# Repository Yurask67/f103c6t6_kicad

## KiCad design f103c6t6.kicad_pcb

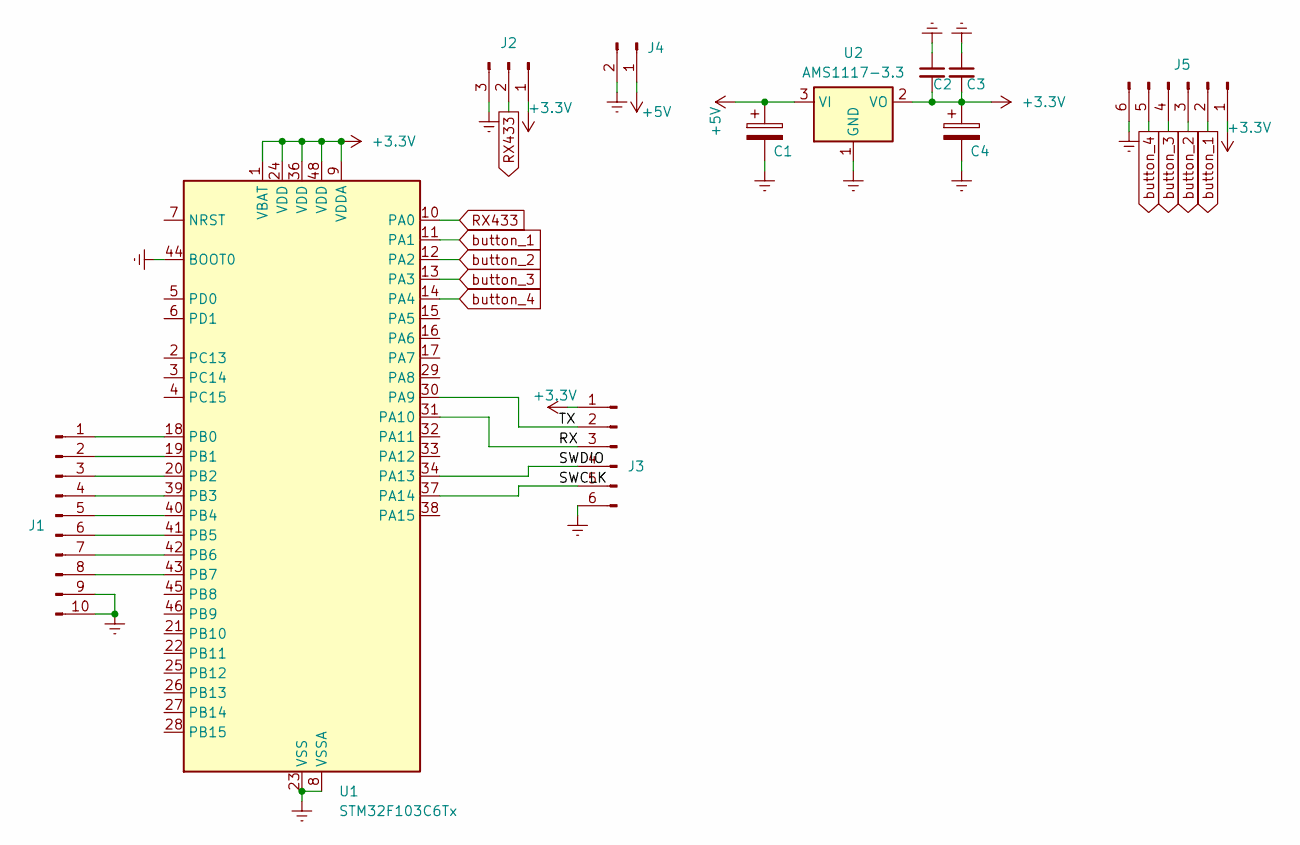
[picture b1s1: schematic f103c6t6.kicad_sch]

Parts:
C1, C4: C_Polarized; CP_Radial_D7.5mm_P2.50mm
C2, C3: C_Small; C_0805_2012Metric_Pad1.18x1.45mm_HandSolder
J1: Conn_01x10_Pin; PinHeader_2x05_P2.54mm_Vertical
J2: Conn_01x03_Pin; PinHeader_1x03_P2.54mm_Vertical
J3, J5: Conn_01x06_Pin; PinHeader_1x06_P2.54mm_Vertical
J4: Conn_01x02_Pin; PinHeader_1x02_P2.54mm_Vertical
U1: STM32F103C6Tx; LQFP-48_7x7mm_P0.5mm
U2: AMS1117-3.3; SOT-223-3_TabPin2

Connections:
+3.3V: C2.2, C3.2, C4.1, J2.1, J3.1, J5.1, U1.1 (VBAT), U1.9 (VDDA), U1.24 (VDD), U1.36 (VDD), U1.48 (VDD), U2.2 (VO)
+5V: C1.1, J4.1, U2.3 (VI)
/RX: J3.3, U1.31 (PA10)
/SWCLK: J3.5, U1.37 (PA14)
/SWDIO: J3.4, U1.34 (PA13)
/TX: J3.2, U1.30 (PA9)
GNDREF: C1.2, C2.1, C3.1, C4.2, J1.9, J1.10, J2.3, J3.6, J4.2, J5.6, U1.8 (VSSA), U1.23 (VSS), U1.35 (VSS), U1.44 (BOOT0), U1.47 (VSS), U2.1 (GND)
unnamed: J1.1, U1.18 (PB0)
unnamed: J1.2, U1.19 (PB1)
unnamed: J1.3, U1.20 (PB2)
unnamed: J1.4, U1.39 (PB3)
unnamed: J1.5, U1.40 (PB4)
unnamed: J1.6, U1.41 (PB5)
unnamed: J1.7, U1.42 (PB6)
unnamed: J1.8, U1.43 (PB7)
RX433: J2.2, U1.10 (PA0)
button_1: J5.2, U1.11 (PA1)
button_2: J5.3, U1.12 (PA2)
button_3: J5.4, U1.13 (PA3)
button_4: J5.5, U1.14 (PA4)

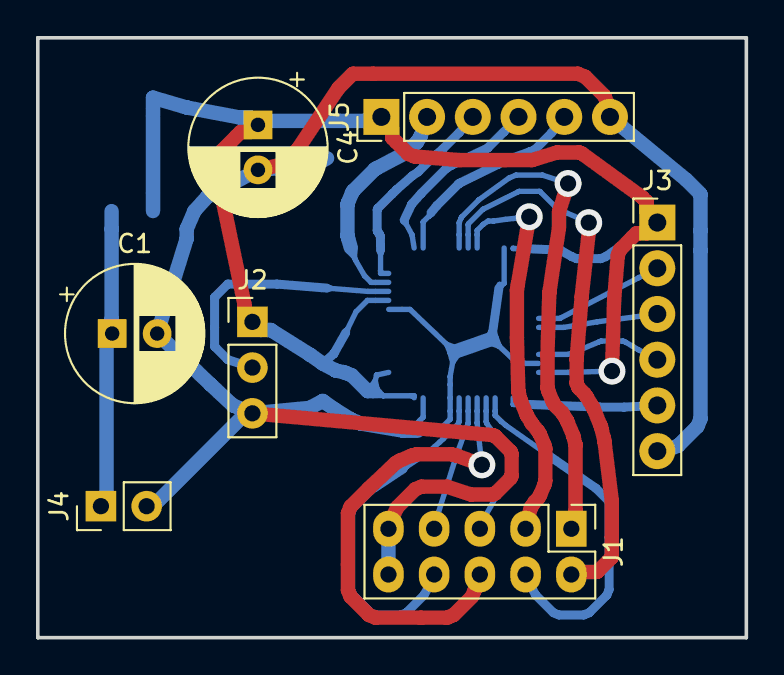
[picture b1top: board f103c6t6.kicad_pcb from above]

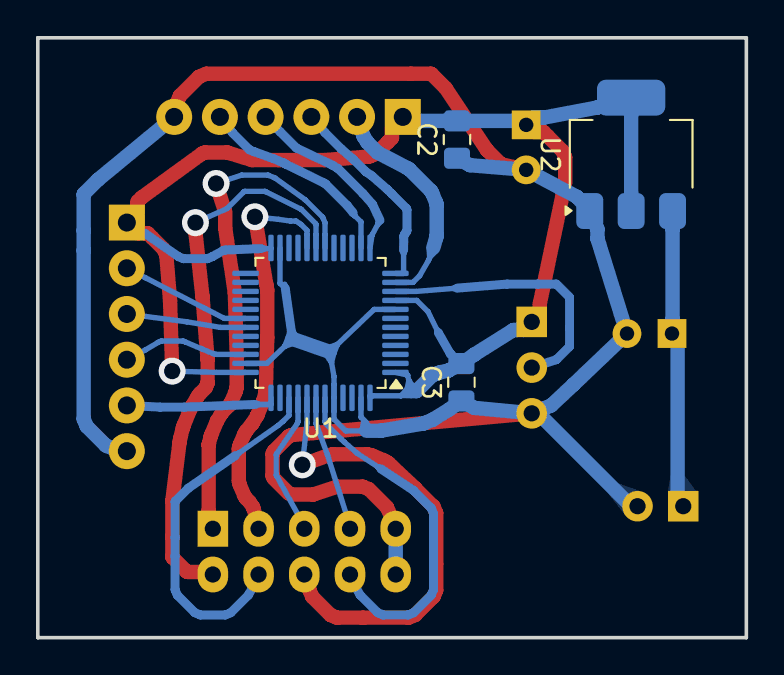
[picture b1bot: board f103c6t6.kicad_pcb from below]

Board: 2 copper layers, 39.4 x 33.3 mm, 11 parts (4 on the bottom side), 20 nets.

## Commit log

2025-03-03 init
2025-03-04 serial +
    Добавлен сериал порт для монитора ардуино
2025-07-29 Gerber
    Экспортированы слои в гербер и дрил для сверловки
2025-11-12 12.11.2025
2025-11-12 Оптимизация
